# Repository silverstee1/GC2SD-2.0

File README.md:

# GC2SD-2.0
GC2SD 2.0 Upgrade PCB

Replacement upgrade PCB for GC2SD sold on aliexpress/amazon etc to V2.0 for use on GameCube's Front Memcard Slot B

Based on the SD2SP2 2.0 made by Extrems, Thank you for your hard work!

**Important**

When using the adapter make sure to have the Latest Version of Swiss, Due to the way Swiss handles it in SLOT A it 
acts like a normal speed Passive SDGecko, in SLOT B it works in Semi-Passive 2.0 enhanced speed mode.

https://github.com/emukidid/swiss-gc

GC2SD 2.0 BOM
=====================================
The PCB must be ordered (e.g. from jlcpcb) in 0.8mm thickness with surface finish ENIG at minimum.

**Note**

R1,D1 are not necessary if you don't want to have LED in your adapter or want to minimize on components.

**GC2SD V2.0 PCB**

**R1:** 0402 470ohm Resistor - Digikey Part# 311-470LRCT-ND (you can use smaller value or larger value depending how bright you want it, 14ohm will be the brightest, I choose 470ohm as its what I had on hand and its not too bright)

LCSC Part# C114877

**D1:** 0402 Green Led 20ma (Dot on PCB footprint marks LED Cathode side) - Digikey Part# 1516-1216-1-ND

LCSC Part# C2856703

or

0402 Blue Led 20ma (Dot on PCB footprint marks LED Cathode side) - Digikey Part# 1516-1215-1-ND

LCSC Part # C965797

**J1:** MicroSD Slot - SOFNG TF-004

LCSC Part# C428454

alt LCSC Part# C20624805 , C410348 , C381081

**U1:** OR Gate IC - DigiKey Part# 296-1093-1-ND

LCSC Part# C7470

Alt Nexperia Digikey Part# 1727-3067-1-ND

LCSC Alt Nexperia Part# C12488

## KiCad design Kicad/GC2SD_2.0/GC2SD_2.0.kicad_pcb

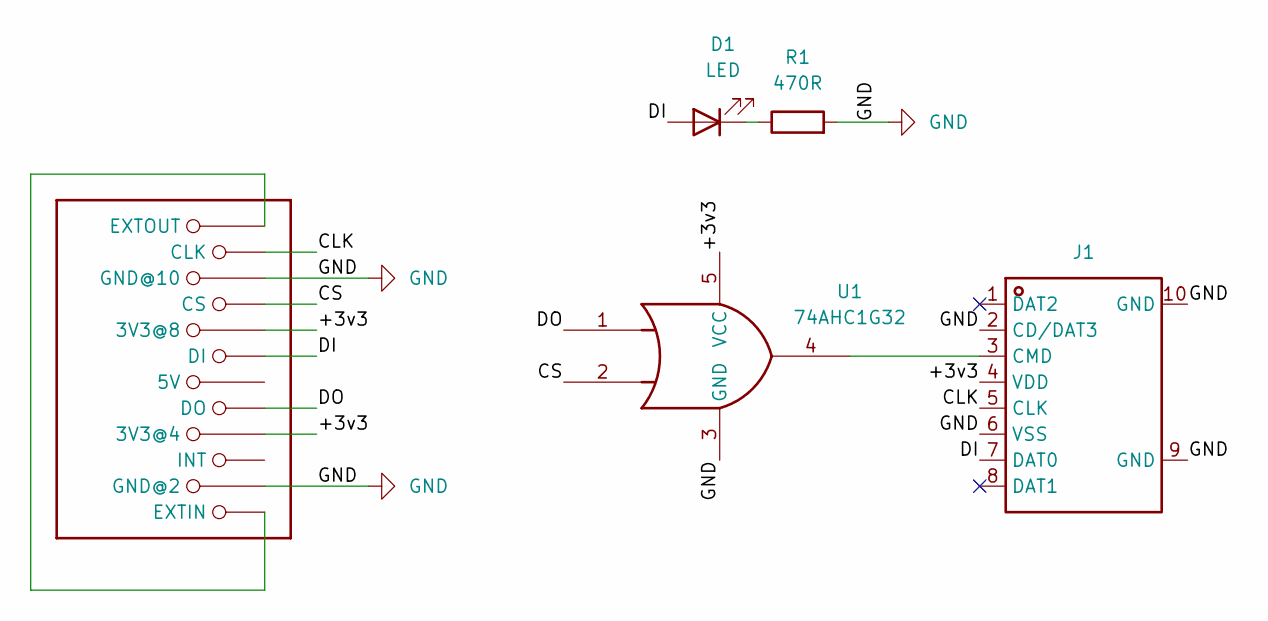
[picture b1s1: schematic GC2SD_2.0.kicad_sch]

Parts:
D1: LED; LED_0402_1005Metric_Pad0.77x0.64mm_HandSolder
J1: TF-004; TF-SMD_TF-004; MANUFACTURER PART TF-004; LCSC PART NAME 拔插式 MicroSD卡(TF卡) 卡座
J2: GC_MEMCARD
R1: 470R; R_0402_1005Metric_Pad0.72x0.64mm_HandSolder
U1: 74AHC1G32; SC-74A-5_1.55x2.9mm_P0.95mm

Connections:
/+3v3: J1.4 (VDD), J2.4 (3V3@4), J2.8 (3V3@8), U1.5 (VCC)
/CLK: J1.5 (CLK), J2.11 (CLK)
/CS: J2.9 (CS), U1.2
/DI: D1.2 (A), J1.7 (DAT0), J2.7 (DI)
/DO: J2.5 (DO), U1.1
GND: J1.2 (CD/DAT3), J1.6 (VSS), J1.9 (GND), J1.10 (GND), J2.2 (GND@2), J2.10 (GND@10), R1.2, U1.3 (GND)
unnamed: D1.1 (K), R1.1
unnamed: J1.3 (CMD), U1.4
unnamed: J2.1 (EXTIN), J2.12 (EXTOUT)

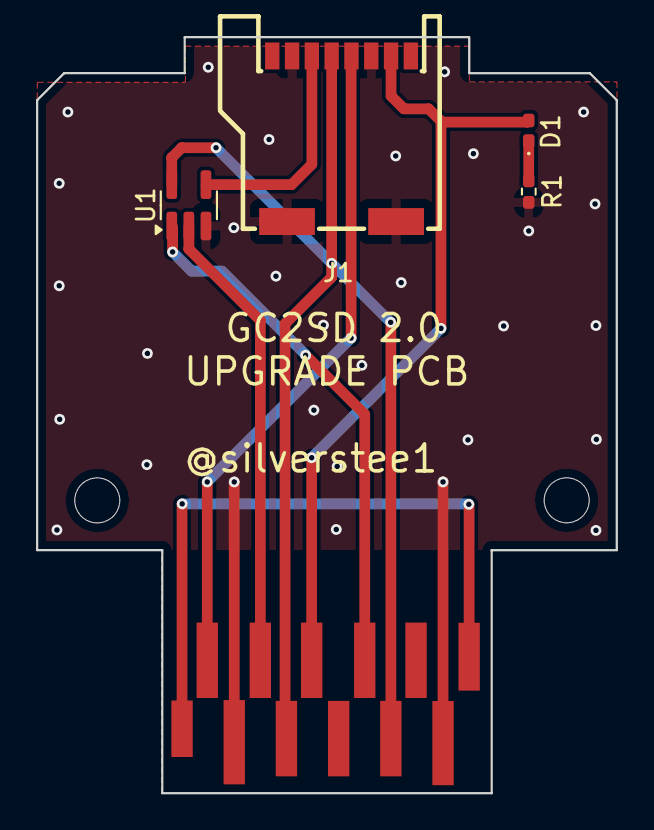
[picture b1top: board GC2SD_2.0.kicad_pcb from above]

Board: 2 copper layers, 32.2 x 42.0 mm, 5 parts (0 on the bottom side), 9 nets.

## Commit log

2024-10-03 added project and pcb gerbers
    uploaded project
2024-10-03 pcb order example
    example of the selected values for pcb order
